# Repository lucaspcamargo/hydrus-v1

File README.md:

# Hydrus v1

Project files for the first version of the Hydrus vehicle (hw, sw, and docs).

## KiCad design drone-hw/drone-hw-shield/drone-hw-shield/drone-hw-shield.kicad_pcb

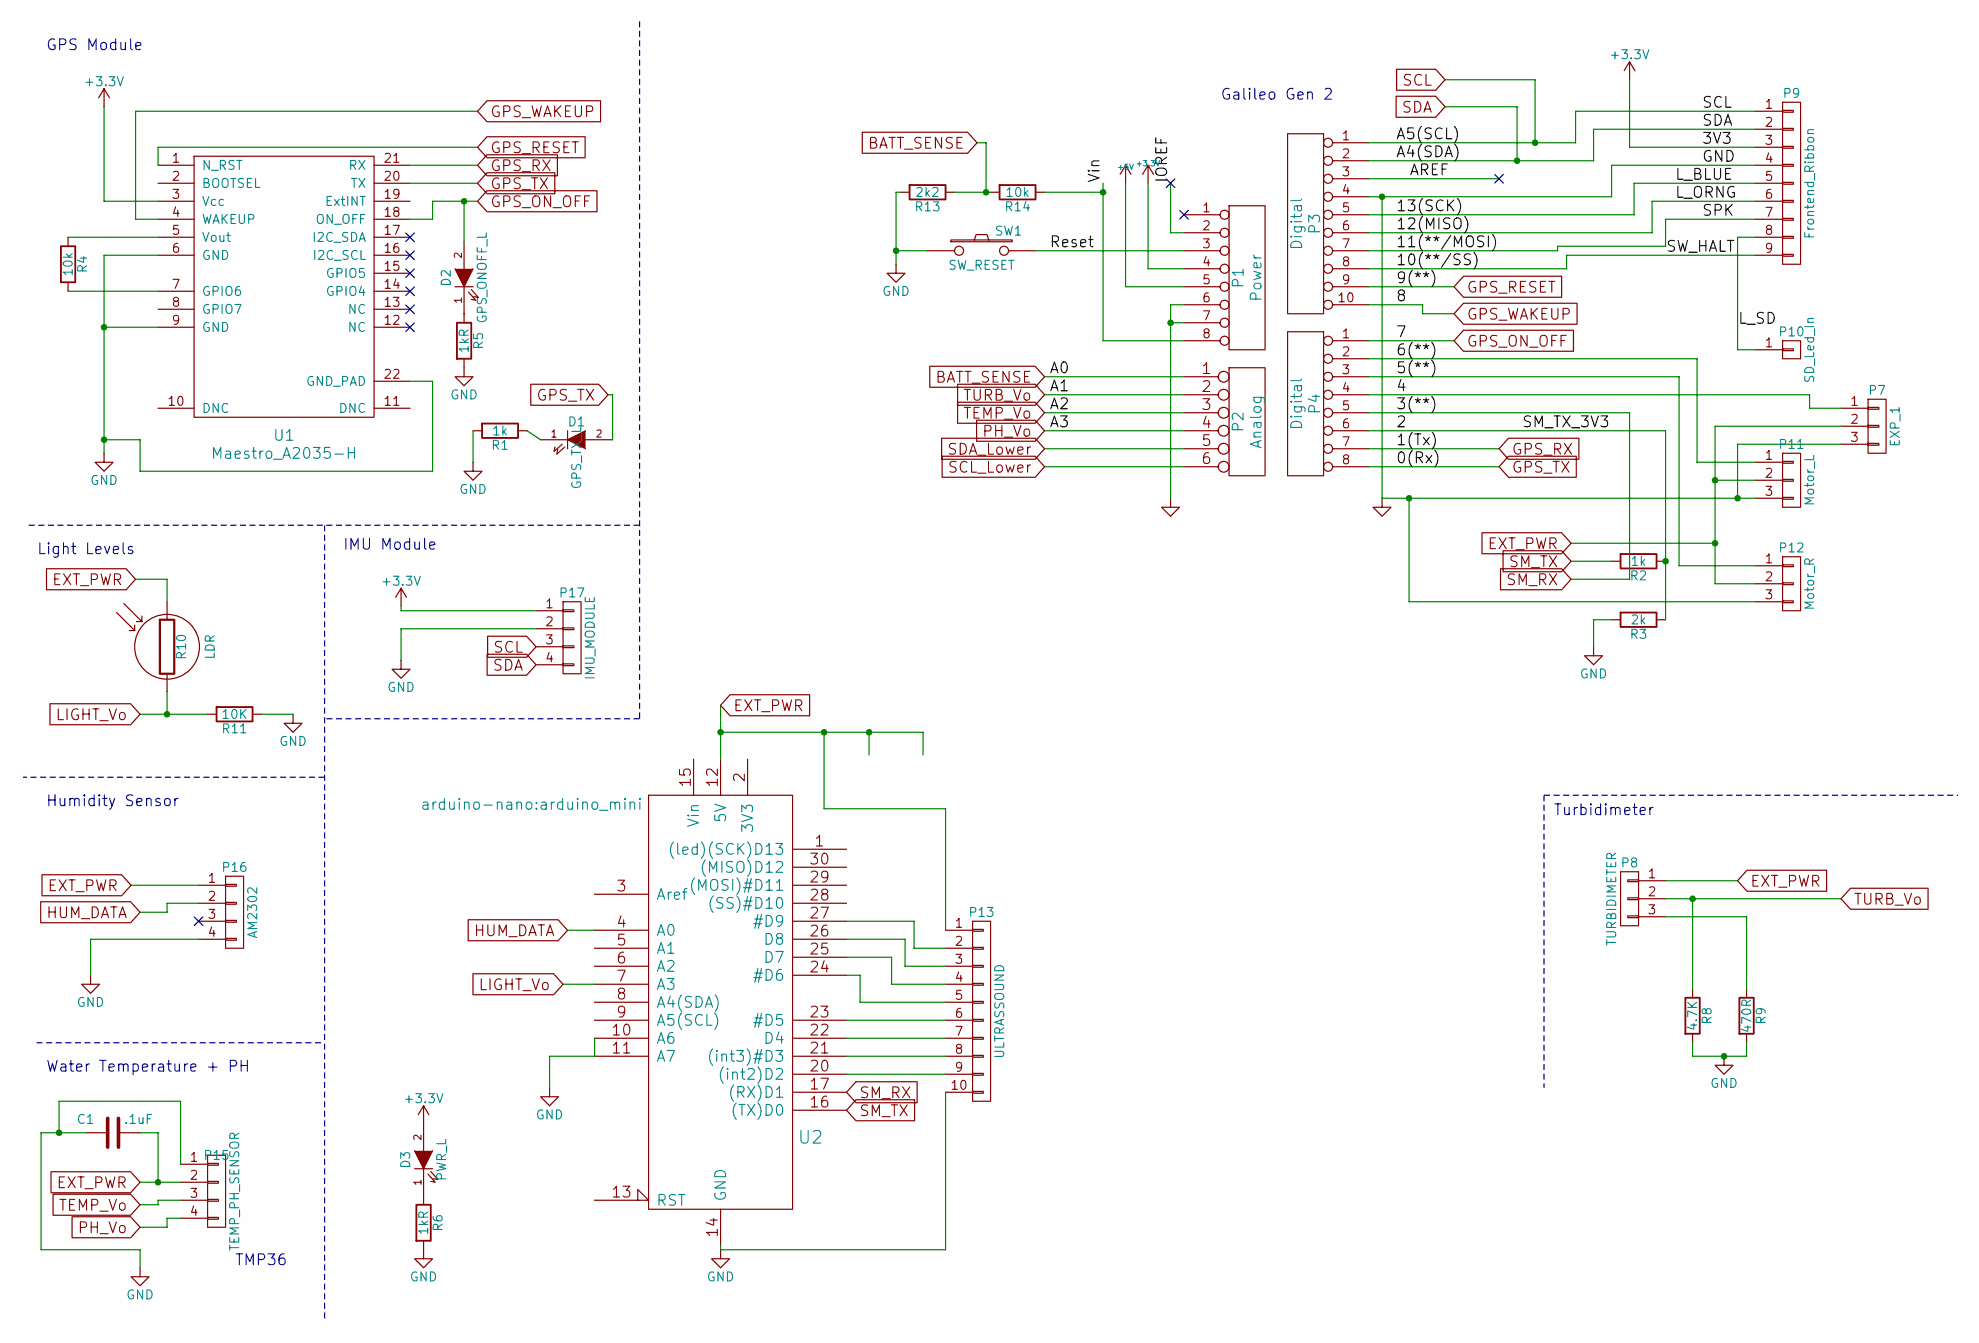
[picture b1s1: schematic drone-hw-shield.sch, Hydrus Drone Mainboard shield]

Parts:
C1: .1uF; C_0805_HandSoldering
D1: GPS_TX_L; LED_1206
D2: GPS_ONOFF_L; LED_1206
D3: PWR_L; LED_1206
P1: Power; Socket_Strip_Arduino_1x08
P2: Analog; Socket_Strip_Arduino_1x06
P3: Digital; Socket_Strip_Arduino_1x10
P4: Digital; Socket_Strip_Arduino_1x08
P7: EXP_1; Pin_Header_Straight_1x03
P8: TURBIDIMETER; Pin_Header_Straight_1x03
P9: Frontend_Ribbon; Pin_Header_Straight_1x09
P10: SD_Led_In; Pin_Header_Straight_1x01
P11: Motor_L; Pin_Header_Straight_1x03
P12: Motor_R; Pin_Header_Straight_1x03
P13: ULTRASSOUND; Pin_Header_Straight_1x10
P15: TEMP_PH_SENSOR; Pin_Header_Straight_1x04
P16: AM2302; Pin_Header_Straight_1x04
P17: IMU_MODULE; Pin_Header_Straight_1x04
R1, R2: 1k; R_0805_HandSoldering
R3: 2k; R_0805_HandSoldering
R4: 10k; R_0805_HandSoldering
R5, R6: 1kR; R_0805_HandSoldering
R8: 4.7K; R_0805_HandSoldering
R9: 470R; R_0805_HandSoldering
R10: LDR; Pin_Header_Straight_1x02
R11: 10K; R_0805_HandSoldering
R13: 2k2; R_0805
R14: 10k; R_0805
SW1: SW_RESET; SW_SPST_SKQG
U1: Maestro_A2035-H; Maestro_Module
U2: Extension Module; arduino_mini

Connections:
+3V3: D3.2 (A), P1.4, P9.3, P17.1, U1.3 (Vcc)
+5V: P1.5
/2: P4.6, R2.1, R3.1
/4: P4.4, P7.1
/5(**): P4.3, P12.1
/6(**): P4.2, P11.1
/10(**/SS): P3.8, P9.9
/11(**/MOSI): P3.7, P9.7
/12(MISO): P3.6, P9.6
/13(SCK): P3.5, P9.5
/AREF: P3.3
/IOREF: P1.2
/L_SD: P9.8, P10.1
/Reset: P1.3, SW1.2
/Vin: P1.8, R14.1
BATT_SENSE: P2.1, R13.1, R14.2
EXT_PWR: C1.2, P7.2, P8.1, P11.2, P12.2, P13.1, P15.2, P16.1, R10.1, U2.12 (5V)
GND: C1.1, P1.6, P1.7, P3.4, P7.3, P9.4, P11.3, P12.3, P13.10, P15.1, P16.4, P17.2, R1.2, R3.2, R5.2, R6.2, R8.2, R9.2, R11.1, R13.2, SW1.1, U1.6 (GND), U1.9 (GND), U1.22 (GND_PAD), U2.10 (A6), U2.11 (A7), U2.14 (GND), U2.19 (GND)
GPS_ON_OFF: D2.2 (A), P4.1, U1.18 (ON_OFF)
GPS_RESET: P3.9, U1.1 (N_RST)
GPS_RX: P4.7, U1.21 (RX)
GPS_TX: D1.2 (A), P4.8, U1.20 (TX)
GPS_WAKEUP: P3.10, U1.4 (WAKEUP)
HUM_DATA: P16.2, U2.4 (A0)
LIGHT_Vo: R10.2, R11.2, U2.7 (A3)
unnamed: D1.1 (K), R1.1
unnamed: D2.1 (K), R5.1
unnamed: D3.1 (K), R6.1
unnamed: P8.3, R9.1
unnamed: P13.2, U2.27 (#D9)
unnamed: P13.3, U2.26 (D8)
unnamed: P13.4, U2.25 (D7)
unnamed: P13.5, U2.24 (#D6)
unnamed: P13.6, U2.23 (#D5)
unnamed: P13.7, U2.22 (D4)
unnamed: P13.8, U2.21 ((int3)#D3)
unnamed: P13.9, U2.20 ((int2)D2)
unnamed: R4.1, U1.5 (Vout)
unnamed: R4.2, U1.7 (GPIO6)
PH_Vo: P2.4, P15.4
SCL: P3.1, P9.1, P17.3
SCL_Lower: P2.6
SDA: P3.2, P9.2, P17.4
SDA_Lower: P2.5
SM_RX: P4.5, U2.17 ((RX)D1)
SM_TX: R2.2, U2.16 ((TX)D0)
TEMP_Vo: P2.3, P15.3
TURB_Vo: P2.2, P8.2, R8.1

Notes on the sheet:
Turbidimeter
GPS Module
Galileo Gen 2
Light Levels
Water Temperature + PH
TMP36
IMU Module
Humidity Sensor

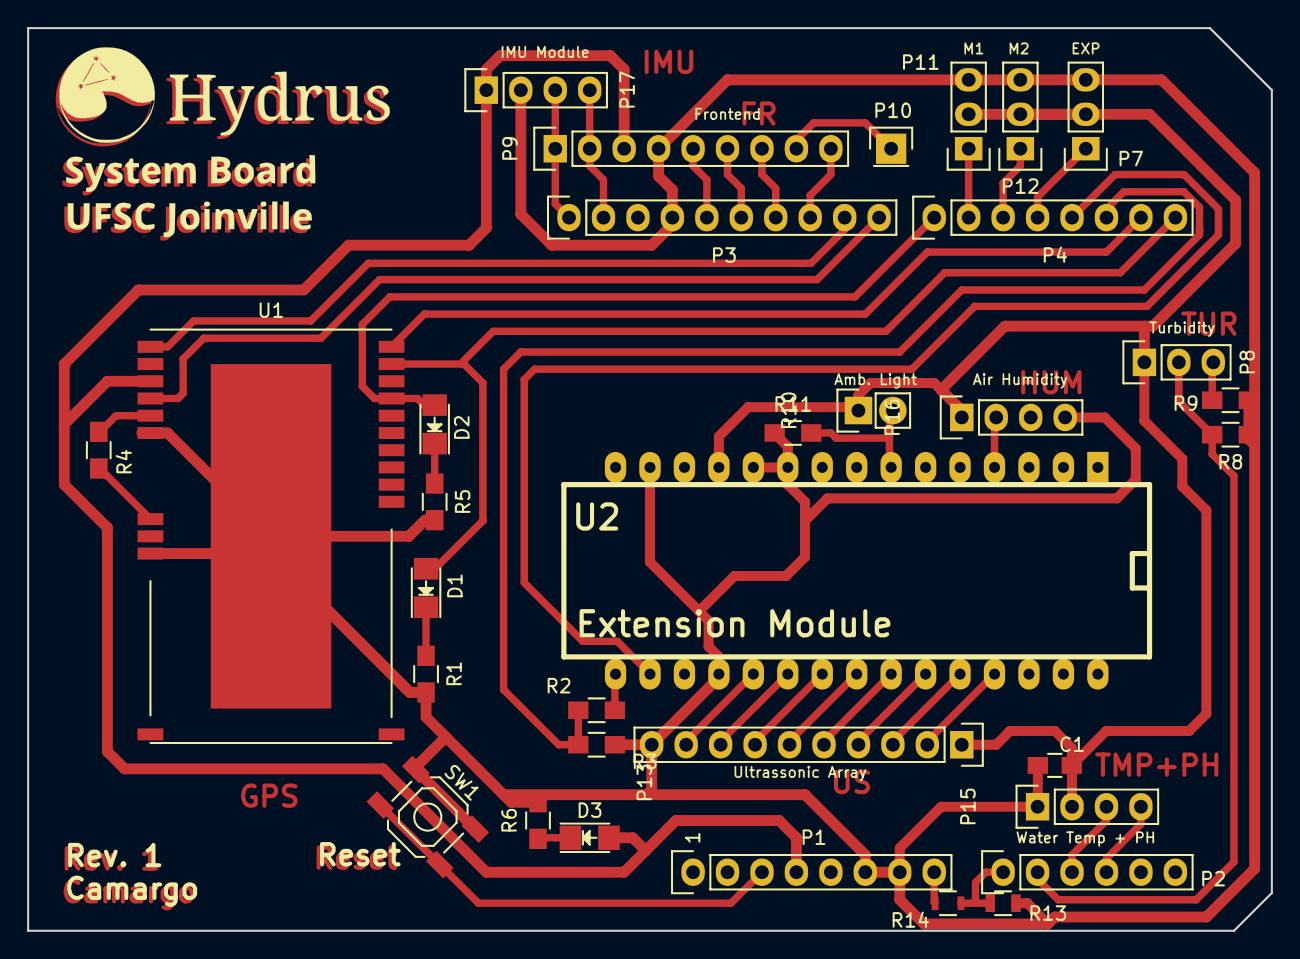
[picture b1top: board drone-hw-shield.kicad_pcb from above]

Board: 2 copper layers, 91.7 x 66.5 mm, 33 parts (0 on the bottom side), 43 nets.

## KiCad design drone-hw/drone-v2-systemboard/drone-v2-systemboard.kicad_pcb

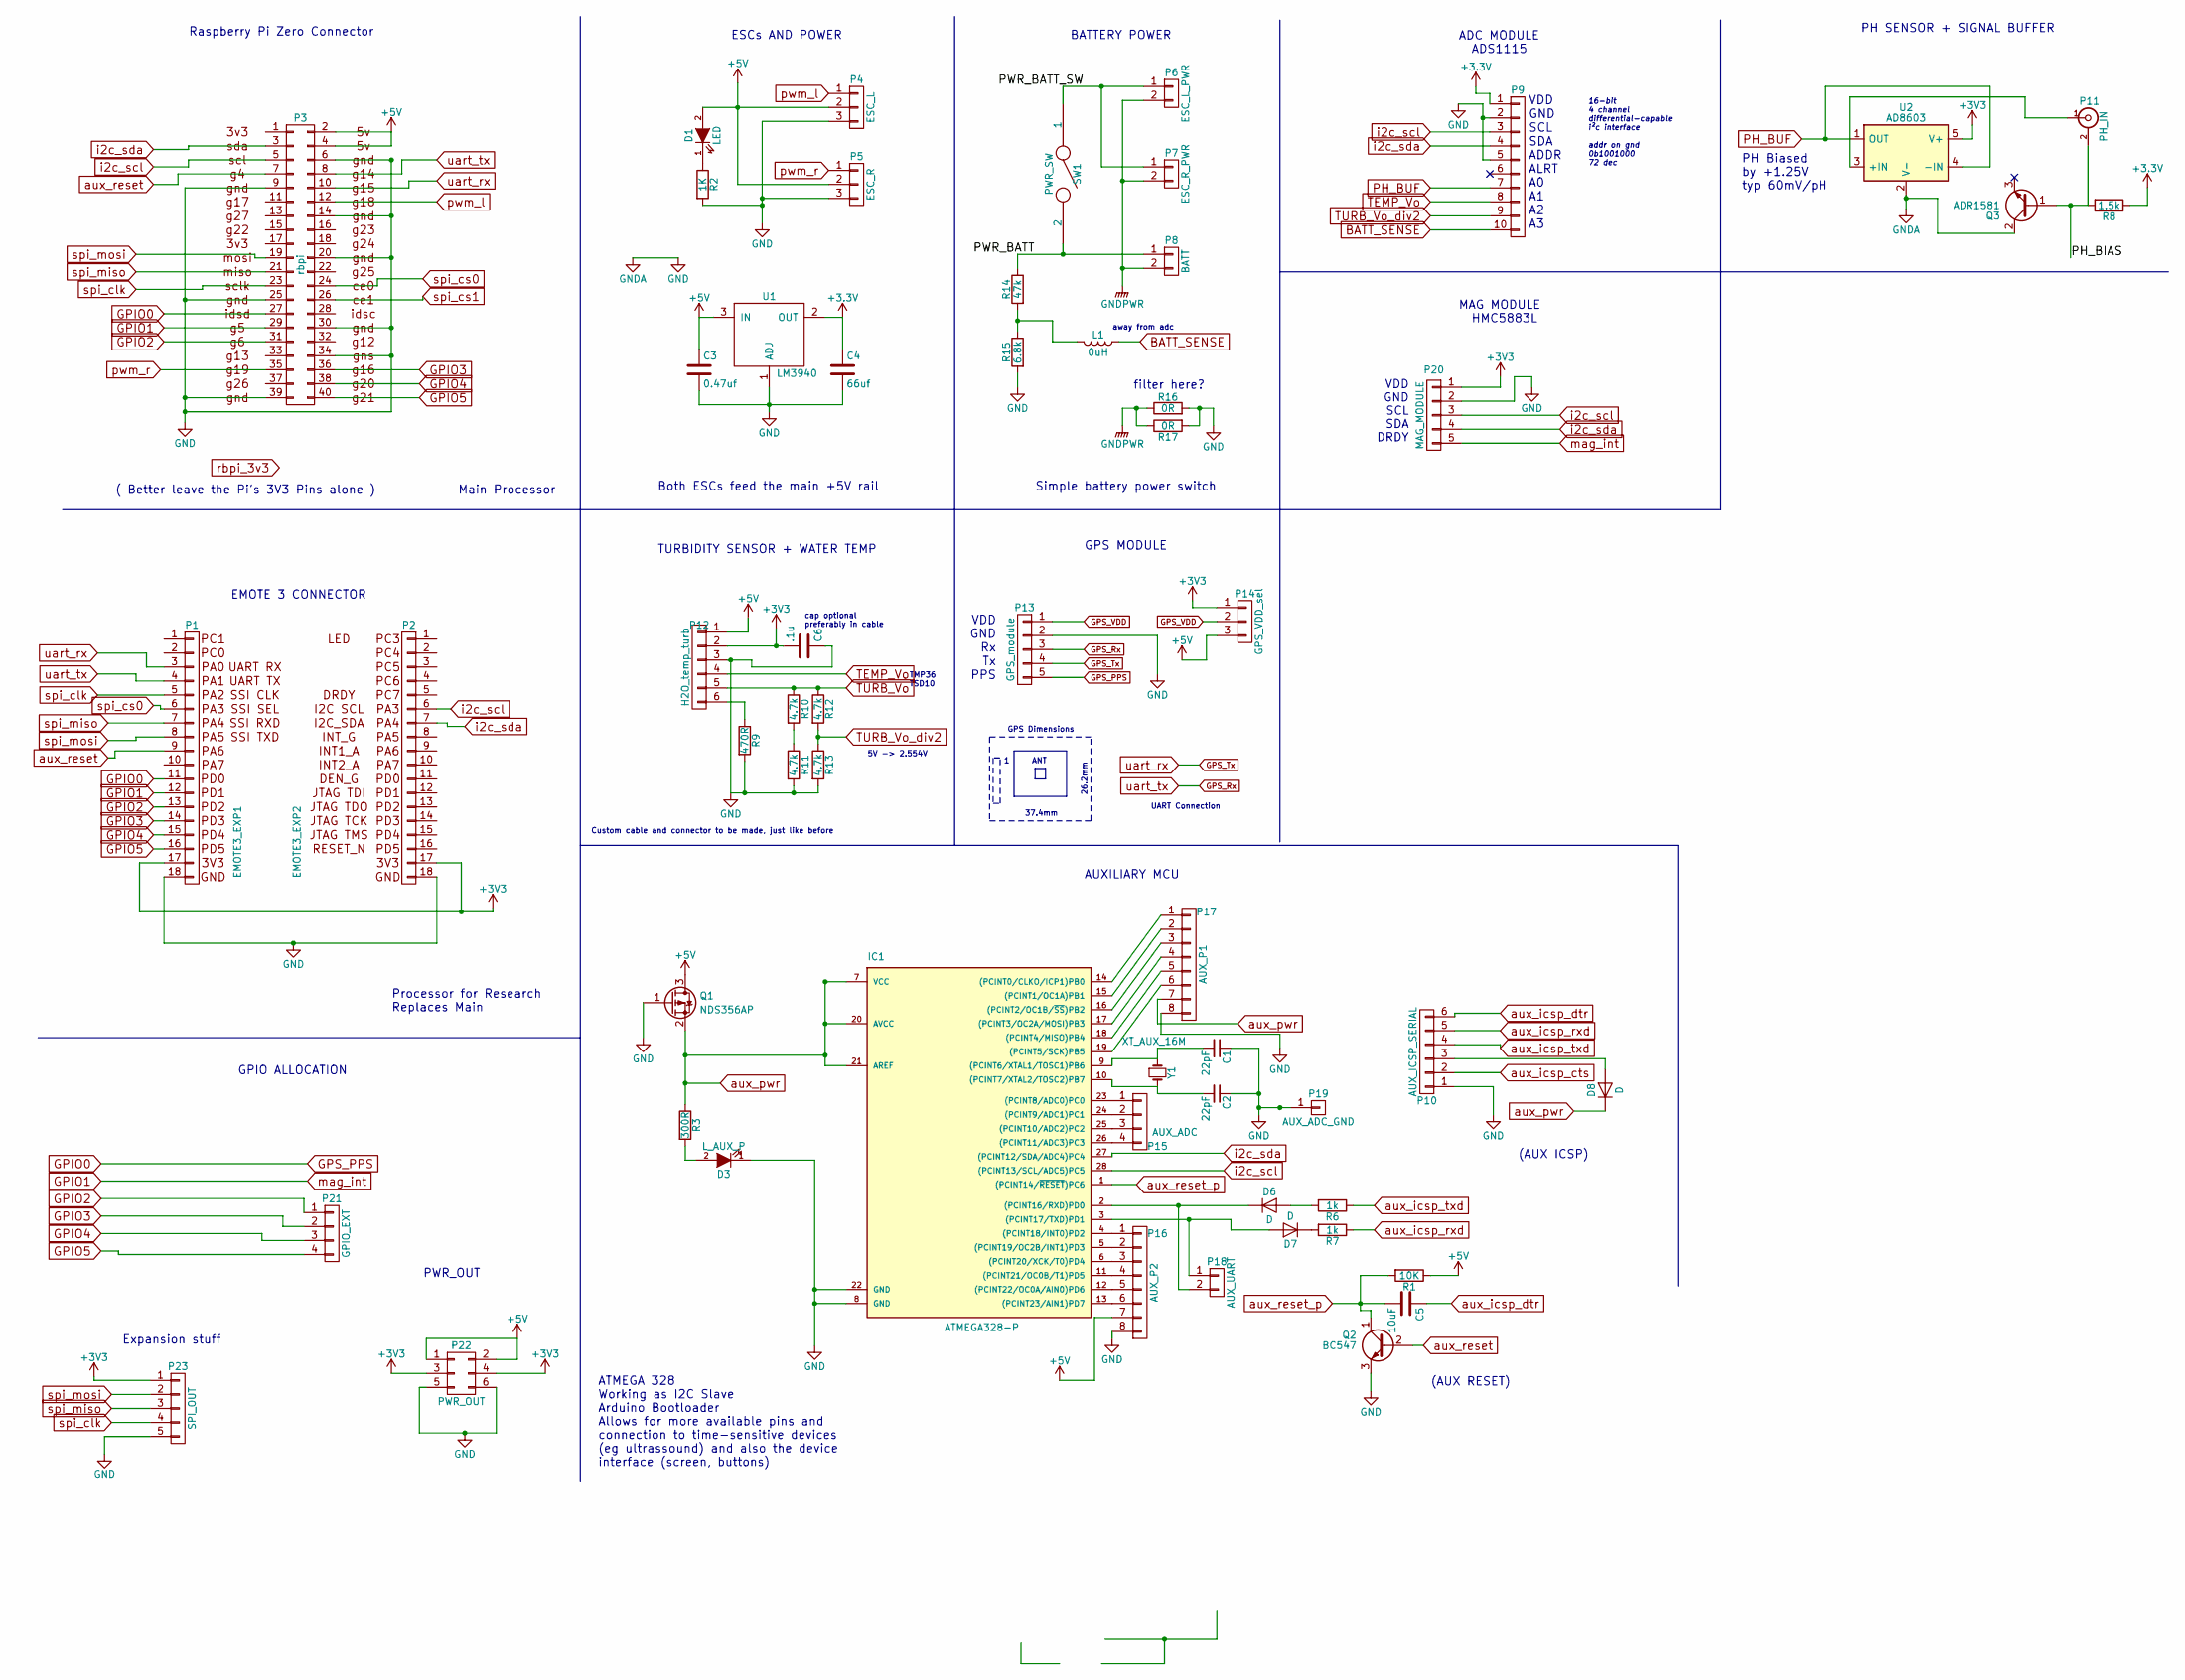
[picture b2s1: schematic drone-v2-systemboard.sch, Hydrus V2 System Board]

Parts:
C1, C2: 22pF; C_0805_HandSoldering
C3: 0.47uf; C_0805_HandSoldering
C4: 66uf; C_0805_HandSoldering
C5: 10uF; CP_Tantalum_Case-S_EIA-3216-12_Hand
C6: .1u; C_0805_HandSoldering
D1: LED; LED-5MM
D3: L_AUX_P; LED_0805
D6, D7, D8: D; D_SOD-123
IC1: ATMEGA328-P; DIP-28_W7.62mm
L1: 0uH; Inductor_1212
P1: EMOTE3_EXP1; HEADER_18x1_EMOTE
P2: EMOTE3_EXP2; HEADER_18x1_EMOTE
P3: rbpi; Pin_Header_Straight_2x20
P4: ESC_L; Pin_Header_Straight_1x03
P5: ESC_R; Pin_Header_Straight_1x03
P6: ESC_L_PWR; AK300-2
P7: ESC_R_PWR; AK300-2
P8: BATT; AK300-2
P9: ADC_MODULE; Pin_Header_Straight_1x10_Pitch2.54mm
P10: AUX_ICSP_SERIAL; Pin_Header_Straight_1x06_Pitch2.54mm
P11: PH_IN; BNC
P12: H2O_temp_turb; Pin_Header_Straight_1x06_Pitch2.54mm
P13: GPS_module; Pin_Header_Straight_1x05_Pitch2.54mm
P14: GPS_VDD_sel; Pin_Header_Straight_1x03_Pitch2.54mm
P15: AUX_ADC; Pin_Header_Straight_1x04_Pitch2.54mm
P16: AUX_P2; Pin_Header_Straight_1x08_Pitch2.54mm
P17: AUX_P1; Pin_Header_Straight_1x08_Pitch2.54mm
P18: AUX_UART; Pin_Header_Straight_1x02_Pitch2.54mm
P19: AUX_ADC_GND; Pin_Header_Straight_1x01_Pitch2.54mm
P20: MAG_MODULE; Pin_Header_Straight_1x05_Pitch2.54mm
P21: GPIO_EXT; Pin_Header_Straight_1x04_Pitch2.54mm
P22: PWR_OUT; Pin_Header_Straight_2x03_Pitch2.54mm
P23: SPI_OUT; Pin_Header_Straight_1x05_Pitch2.54mm
Q1: NDS356AP; SuperSOT-3
Q2: BC547; TO-92_Inline_Wide
Q3: ADR1581; SOT-23
R1: 10K; R_0805_HandSoldering
R2: 1K; R_0805_HandSoldering
R3: 300R; R_0805_HandSoldering
R6, R7: 1k; R_0805_HandSoldering
R8: 1.5k; R_0805_HandSoldering
R9: 470R; R_0805_HandSoldering
R10, R11, R12, R13: 4.7k; R_0805_HandSoldering
R14: 47k; R_0805_HandSoldering
R15: 6.8k; R_0805_HandSoldering
R16, R17: 0R; R_1210_HandSoldering
SW1: PWR_SW; AK300-2
U1: LM3940; SOT-223-3Lead_TabPin2
U2: AD8603; TSOT-23-5_HandSoldering
Y1: XT_AUX_16M; Crystal_HC49-U_Vertical

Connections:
+5V: C3.1, D1.2 (A), P3.2, P3.4, P4.2, P5.2, P12.1, P14.3, P16.7, P22.1, P22.2, Q1.3 (D), R1.1, U1.3 (IN)
/PH_BIAS: P11.2 (Ext), Q3.1 (B), R8.2
/PWR_BATT: P8.1, R14.1, SW1.2
/PWR_BATT_SW: P6.1, P7.1, SW1.1
BATT_SENSE: L1.1, P9.10
GND: C1.1, C2.1, C3.2, C4.2, C6.1, D3.1 (K), IC1.8 (GND), IC1.22 (GND), P1.18, P2.18, P3.6, P3.9, P3.14, P3.20, P3.25, P3.30, P3.34, P3.39, P4.3, P5.3, P9.2, P9.5, P10.1, P12.3, P13.2, P16.8, P17.8, P19.1, P20.2, P22.5, P22.6, P23.5, Q1.1 (G), Q2.3 (E), Q3.2 (C), R2.2, R9.2, R11.2, R13.2, R15.2, R16.2, R17.2, U1.1 (ADJ), U2.2 (V-)
GNDPWR: P6.2, P7.2, P8.2, R16.1, R17.1
GPIO0: P1.11, P3.27, P13.5
GPIO1: P1.12, P3.29, P20.5
GPIO2: P1.13, P3.31, P21.1
GPIO3: P1.14, P3.36, P21.2
GPIO4: P1.15, P3.38, P21.3
GPIO5: P1.16, P3.40, P21.4
GPS_Rx: P1.4, P3.8, P13.3
GPS_Tx: P1.3, P3.10, P13.4
GPS_VDD: P13.1, P14.2
unnamed: C1.2, IC1.9 ((PCINT6/XTAL1/TOSC1)PB6), Y1.1
unnamed: C2.2, IC1.10 ((PCINT7/XTAL2/TOSC2)PB7), Y1.2
unnamed: D1.1 (K), R2.1
unnamed: D3.2 (A), R3.2
unnamed: D6.1 (K), IC1.2 ((PCINT16/RXD)PD0), P18.2
unnamed: D6.2 (A), R6.2
unnamed: D7.1 (K), R7.2
unnamed: D7.2 (A), IC1.3 ((PCINT17/TXD)PD1), P18.1
unnamed: D8.2 (A), P10.3
unnamed: IC1.4 ((PCINT18/INT0)PD2), P16.1
unnamed: IC1.5 ((PCINT19/OC2B/INT1)PD3), P16.2
unnamed: IC1.6 ((PCINT20/XCK/T0)PD4), P16.3
unnamed: IC1.11 ((PCINT21/OC0B/T1)PD5), P16.4
unnamed: IC1.12 ((PCINT22/OC0A/AIN0)PD6), P16.5
unnamed: IC1.13 ((PCINT23/AIN1)PD7), P16.6
unnamed: IC1.14 ((PCINT0/CLKO/ICP1)PB0), P17.1
unnamed: IC1.15 ((PCINT1/OC1A)PB1), P17.2
unnamed: IC1.16 ((PCINT2/OC1B/~SS~)PB2), P17.3
unnamed: IC1.17 ((PCINT3/OC2A/MOSI)PB3), P17.4
unnamed: IC1.18 ((PCINT4/MISO)PB4), P17.5
unnamed: IC1.19 ((PCINT5/SCK)PB5), P17.6
unnamed: IC1.23 ((PCINT8/ADC0)PC0), P15.1
unnamed: IC1.24 ((PCINT9/ADC1)PC1), P15.2
unnamed: IC1.25 ((PCINT10/ADC2)PC2), P15.3
unnamed: IC1.26 ((PCINT11/ADC3)PC3), P15.4
unnamed: L1.2, R14.2, R15.1
unnamed: P11.1 (In), U2.3 (+IN)
unnamed: P12.6, R9.1
unnamed: R10.2, R11.1
PH_BUF: P9.7, U2.1 (OUT), U2.4 (-IN)
TEMP_Vo: P9.8, P12.4
TURB_Vo: P12.5, R10.1, R12.1
TURB_Vo_div2: P9.9, R12.2, R13.1
aux_icsp_dtr: C5.1, P10.6
aux_icsp_rxd: P10.5, R7.1
aux_icsp_txd: P10.4, R6.1
aux_pwr: D8.1 (K), IC1.7 (VCC), IC1.20 (AVCC), IC1.21 (AREF), P17.7, Q1.2 (S), R3.1
aux_reset: P1.9, P3.7, Q2.2 (B)
aux_reset_p: C5.2, IC1.1 ((PCINT14/~RESET~)PC6), Q2.1 (C), R1.2
i2c_scl: IC1.28 ((PCINT13/SCL/ADC5)PC5), P2.6, P3.5, P9.3, P20.3
i2c_sda: IC1.27 ((PCINT12/SDA/ADC4)PC4), P2.7, P3.3, P9.4, P20.4
pwm_l: P3.12, P4.1
pwm_r: P3.35, P5.1
spi_clk: P1.5, P3.23, P23.4
spi_cs0: P1.6, P3.24
spi_miso: P1.7, P3.21, P23.3
spi_mosi: P1.8, P3.19, P23.2

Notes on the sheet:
EMOTE 3 CONNECTOR
Raspberry Pi Zero Connector
ESCs AND POWER
BATTERY POWER
AUXILIARY MCU
ADC MODULE ADS1115
(AUX RESET)
(AUX ICSP)
PH SENSOR + SIGNAL BUFFER
Both ESCs feed the main +5V rail
Simple battery power switch
TURBIDITY SENSOR + WATER TEMP
Main Processor
Processor for Research Replaces Main
PH Biased by +1.25V typ 60mV/pH
VDD GND SCL SDA ADDR ALRT A0 A1 A2 A3
16-bit 4 channel differential-capable i²c interface addr on gnd 0b1001000 72 dec
filter here?
away from adc
GPIO ALLOCATION
TMP36 TSD10
GPS MODULE
VDD GND Rx Tx PPS
26.2mm
37.4mm
ANT
GPS Dimensions
Custom cable and connector to be made, just like before
5V -> 2.554V
cap optional preferably in cable
VDD GND SCL SDA DRDY
MAG MODULE HMC5883L
ATMEGA 328 Working as I2C Slave Arduino Bootloader Allows for more available pins and connection to time-sensitive devices (eg ultrassound) and also the device interface (screen, buttons)
UART Connection
PWR_OUT
Expansion stuff
( Better leave the Pi's 3V3 Pins alone )

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
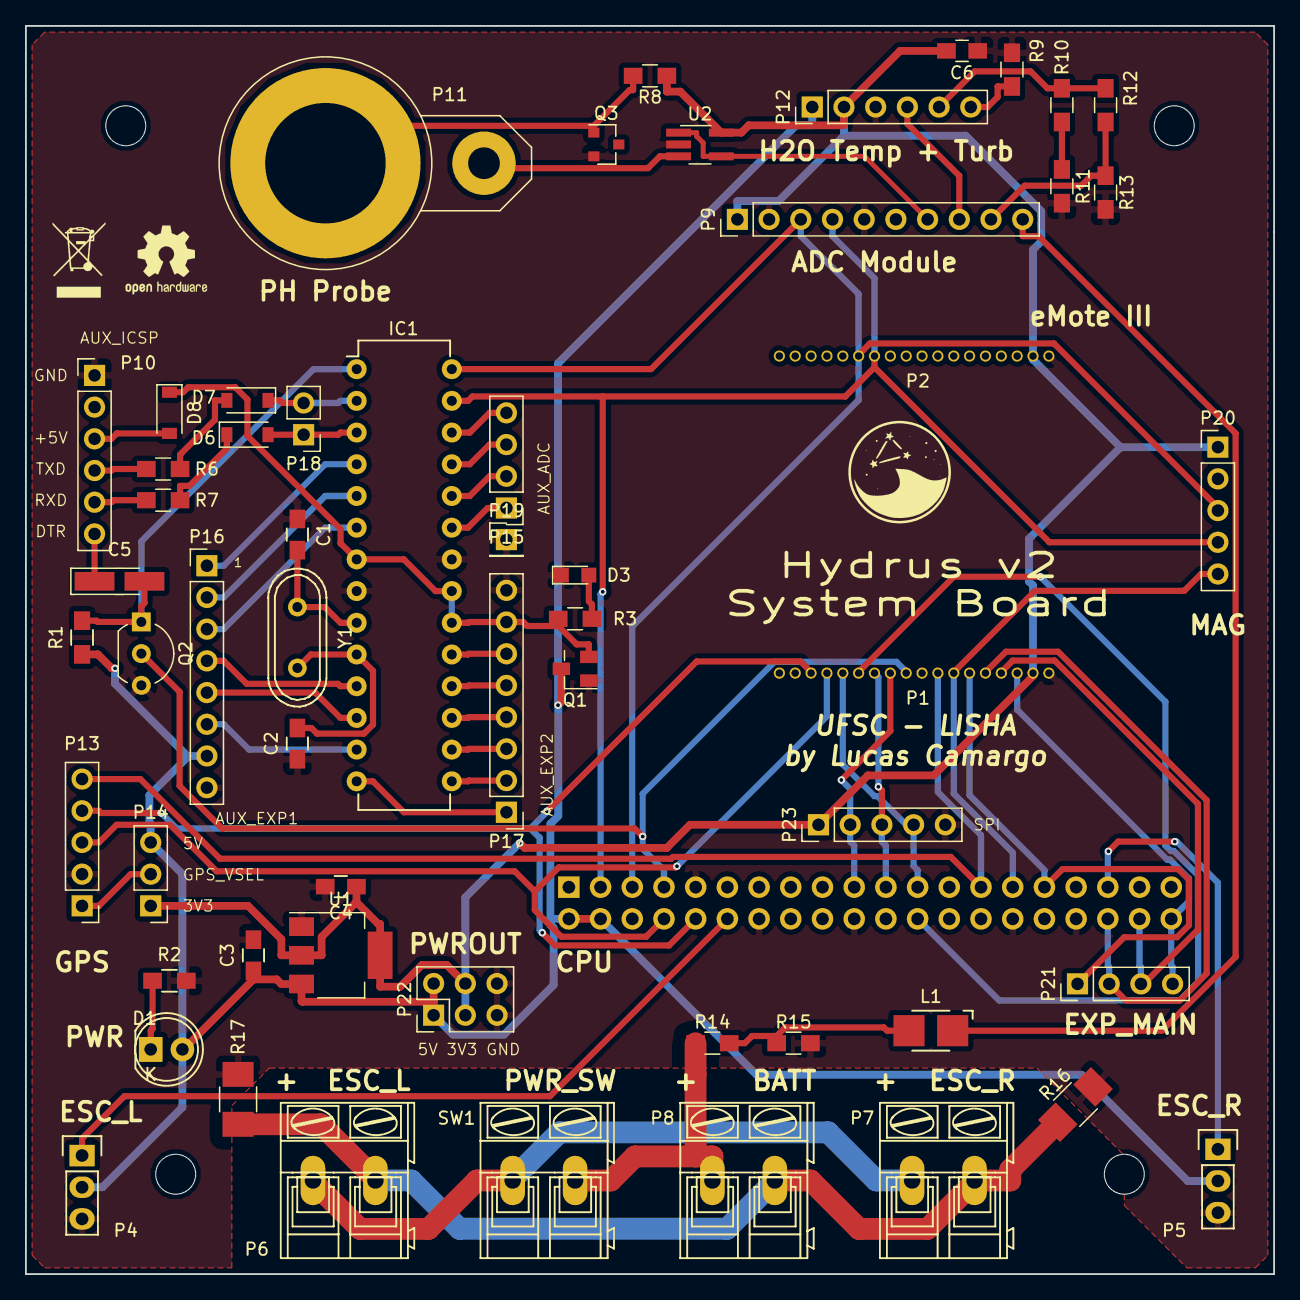
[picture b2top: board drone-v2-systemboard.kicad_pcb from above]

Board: 2 copper layers, 100.0 x 100.0 mm, 64 parts (1 on the bottom side), 64 nets.

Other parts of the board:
HOLE1, HOLE2, HOLE3, HOLE4: MountingHole_3.2mm_M3_DIN965
oshwlogo: OSHW-Logo2_7.3x6mm_SilkScreen
weeelogo: WEEE-Logo_4.2x6mm_SilkScreen

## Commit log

2018-08-02 Initial import
2018-08-02 deleted useless things
2018-08-03 another dummy
2018-08-03 revert dummy
2018-08-03 testing github mirroring
